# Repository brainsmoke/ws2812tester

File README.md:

# Padauk based WS2812 LED tester #

* tests using low brightness [0..15] & temporal dithering for a smooth animation
* Tests using a 3v3 data signal (which should be OK for V5 LEDs)

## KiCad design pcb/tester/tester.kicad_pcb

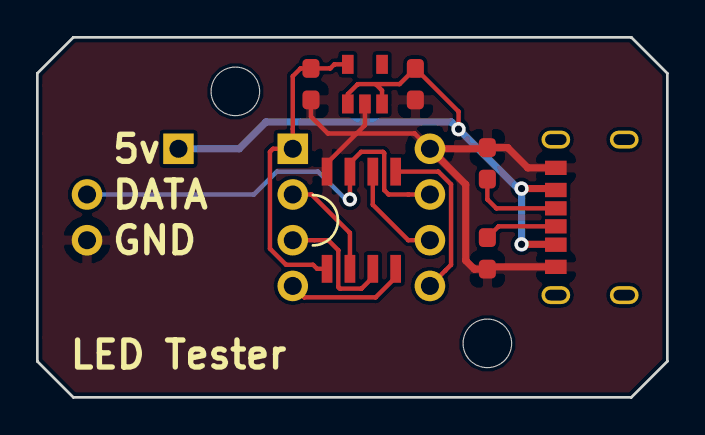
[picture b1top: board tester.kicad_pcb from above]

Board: 2 copper layers, 35.0 x 20.0 mm, 11 parts (0 on the bottom side), 11 nets.

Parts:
C1, C2: C; C_0603_1608Metric_Pad1.05x0.95mm_HandSolder
J1: USB_C_Receptacle_USB2.0; TYPE-C-31-M-17
J2: Conn_01x01_Male; PinHeader_1x01_P2.54mm_Vertical
J3: Conn_01x02_Male; PinHeader_1x02_P2.54mm_Vertical
J4, J5: Conn_01x04_Male; PinHeader_1x04_P2.54mm_Vertical
R1, R2: 5.1k; R_0603_1608Metric_Pad1.05x0.95mm_HandSolder
U1: PIC12F1501-ISN; SOIC-8_3.9x4.9mm_P1.27mm
U2: AP2204K-3.3; SOT-23-5

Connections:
3V3: C2.1, J5.1, U1.1, U2.5
GND: C1.2, C2.2, J1.A1, J3.2, J4.1, R1.1, R2.1, U1.8, U2.2
unnamed: J1.A5, R1.2
unnamed: J1.B5, R2.2
unnamed: J3.1, J4.2, U1.7
unnamed: J4.3, U1.6
unnamed: J4.4, U1.5
unnamed: J5.2, U1.2
unnamed: J5.3, U1.3
unnamed: J5.4, U1.4
VCC: C1.1, J1.A4, J2.1, U2.1, U2.3

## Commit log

2021-01-20 Padauk based ws2812 led strip tester (64 leds)
2021-01-20 add readme
2022-02-12 fix addressing bug for pms150c
2023-12-15 make test program output the same color for all leds
